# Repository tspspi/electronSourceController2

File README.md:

# Electron gun power supply and monitoring controller

_Note_: This project is designed for a particular experiment so it will not
be much of use for anyone who's not working on exactly that experiment.

This is firmware for a simple electron gun controller that is controlling

* Up to four FUG HCP 14-6500 high voltage power supplies (acceleration
  voltage, Wehnelt cylinder, focus voltage and a single deflection voltage
  power supply)
* The voltage and current measured by FUG HCP 14-6500 can also be used for
  general monitoring and beam loss measurement

## External communication ports

* UART0 provides main communication interface (and is also used by avrdude
  during flashing - there is an Arduino bootloader flashed on the board so
  flash method ```ẁiring``` can be used via USB

* Other UARTs may be used for RS485 or other components later on

## Pin assignment

| Pin | Assignment                          | Mode                      | ATEMGA2560 Port / Pin |
| --- | ----------------------------------- | ------------------------- | --------------------- |
| 22  | PSU1: Output enable                 | Digital out (optocoupled) | PA0                   |
| 23  | PSU1: Polarity set                  | Digital out (optocoupled) | PA1                   |
| 24  | PSU1: Current control mode          | Digital in                | PA2                   |
| 25  | PSU1: Voltage control mode          | Digital in                | PA3                   |
| 42  | PSU1: Voltage set                   | Analog out                | PL7                   |
| 43  | PSU1: Current limit set             | Analog out                | PL6                   |
| A0  | PSU1: Voltage sense                 | Analog in                 | PF0                   |
| A1  | PSU1: Current sense                 | Analog in                 | PF1                   |
| 26  | PSU2: Output enable                 | Digital out (optocoupled) | PA4                   |
| 27  | PSU2: Polarity set                  | Digital out (optocoupled) | PA5                   |
| 28  | PSU2: Current control mode          | Digital in                | PA6                   |
| 29  | PSU2: Voltage control mode          | Digital in                | PA7                   |
| 44  | PSU2: Voltage set                   | Analog out                | PL5                   |
| 45  | PSU2: Current limit set             | Analog out                | PL4                   |
| A2  | PSU2: Voltage sense                 | Analog in                 | PF2                   |
| A3  | PSU2: Current sense                 | Analog in                 | PF3                   |
| 30  | PSU3: Output enable                 | Digital out (optocoupled) | PC7                   |
| 31  | PSU3: Polarity set                  | Digital out (optocoupled) | PC6                   |
| 32  | PSU3: Current control mode          | Digital in                | PC5                   |
| 33  | PSU3: Voltage control mode          | Digital in                | PC4                   |
| 46  | PSU3: Voltage set                   | Analog out                | PL3                   |
| 47  | PSU3: Current limit set             | Analog out                | PL2                   |
| A4  | PSU3: Voltage sense                 | Analog in                 | PF4                   |
| A5  | PSU3: Current sense                 | Analog in                 | PF5                   |
| 34  | PSU4: Output enable                 | Digital out (optocoupled) | PC3                   |
| 35  | PSU4: Polarity set                  | Digital out (optocoupled) | PC2                   |
| 36  | PSU4: Current control mode          | Digital in                | PC1                   |
| 37  | PSU4: Voltage control mode          | Digital in                | PC0                   |
| 48  | PSU4: Voltage set                   | Analog out                | PL1                   |
| 49  | PSU4: Current limit set             | Analog out                | PL0                   |
| A6  | PSU4: Voltage sense                 | Analog in                 | PF6                   |
| A7  | PSU4: Current sense                 | Analog in                 | PF7                   |
| 38  | Filament power supply (230V side)   | Digital out               | PD7                   |
| A8  | Current sensor for filament         | Analog in                 | PK0                   |
| 50  | AD7705 MISO                         | Digital in                | PB3                   |
| 51  | AD7705 MOSI                         | Digital out               | PB2                   |
| 52  | AD7705 SCK                          | Digital out               | PB1                   |
| 53  | AD7705 CS                           | Digital out               | PB0                   |
|PWM10| AD7705 Reset                        | Digital out               | PB4                   |
|PWM11| AD7705 data ready                   | Digital in                | PB5                   |

## Protocol

In contrast to other implementations this board supports an ASCII based
communication protocol. For synchronization all messages start with a
fixed synchronization pattern consisting of three dollar signs. Each command
is terminated via a CR LF or only LF (CR is simply ignored by the serial
parser). Numbers are transmitted as ASCII decimal numbers.

| Command                                 | Sequence               | Response                                                                                                                     | Status                           |
| --------------------------------------- | ---------------------- | ---------------------------------------------------------------------------------------------------------------------------- | -------------------------------- |
| ID                                      | $$$ID<LF>              | Sends a simple ID response that identifies the firmware (ex. ```$$$electronctrl_20210707_001<LF>```)                         | working, tested                  |
| Filament on                             | $$$FILON<LF>           | Switches filament power supply on                                                                                            | working, tested                  |
| Filament off                            | $$$FILOFF<LF>          | Switches filament power supply off                                                                                           | working, tested                  |
| Estimate beam current                   | $$$BEAMA<LF>           | Calculates estimated beam current in 1/10 of microamperes                                                                    |                                  |
| Beam on                                 | $$$BEAMON<LF>          | Switches beam high voltage on (slowly, performing insulation test)                                                           | working, tested                  |
| Beam HV off                             | $$$BEAMHVOFF<LF>       | Switches beam high voltage off                                                                                               | working, tested                  |
| Get PSU current                         | $$$PSUGETA[n]<LF>      | Gets current for power supply 1,2,3,4                                                                                        | working, tested                  |
| Get PSU voltage                         | $$$PSUGETV[n]<LF>      | Gets voltage for power supply 1,2,3,4                                                                                        | working, tested                  |
| Get PSU modes                           | $$$PSUMODE<LF>         | Gets the mode for each PSU as a sequence of 4 ASCII chars (A or V for current or voltage controled mode, - for disabled)     | working, tested                  |
| Set PSU current limit                   | $$$PSUSETA[n][mmm]<LF> | Sets the power supply current limit for one of the 4 PSUs. The limit is supplied in 1/10 of an microampere                   | working, tested                  |
| Set PSU target voltage                  | $$$PSUSETV[n][mmm]<LF> | Sets the power supply voltage for one of the 4 PSUs. The voltage is set in V                                                 | working, tested                  |
| Set PSU polarity                        | $$$PSUPOL[n][p/n]<LF>  | Sets the polarity to be positive or negative                                                                                 | working, tested                  |
| Set PSU output enable                   | $$$PSUON[n]<LF>        | Enabled the output of the given PSU                                                                                          | working, tested                  |
| Set PSU output disable                  | $$$PSUOFF[n]<LF>       | Disabled the output of the given PSU                                                                                         | working, tested                  |
| Disable all voltages (PSU and filament) | $$$OFF<LF>             | Disabled all voltages including the filament supply                                                                          | working, tested                  |
| Get filament voltage                    | $$$FILV<LF>            | Measures filament voltage (if supported)                                                                                     |                                  |
| Get filament current                    | $$$FILA<LF>            | Measures filament current (if supported)                                                                                     |                                  |
| Set filament current                    | $$$SETFILA[n]<LF>      | Sets filament current via current controller board                                                                           |                                  |
| Perform HV insulation test              | $$$INSUL<LF>           | Performs insulation test. Reports voltages while testing.                                                                    | working, tested                  |
| Perform cathode bakeout                 | $$$FILBAKE<LF>         | Performs a baking sequence on filament to remove any residue of trapped gas on the surface                                   |                                  |
| Perform software reset                  | $$$RESET<LF>           | Performs a software reset on the control system (reinitializes everything, no power cycle)                                   |                                  |

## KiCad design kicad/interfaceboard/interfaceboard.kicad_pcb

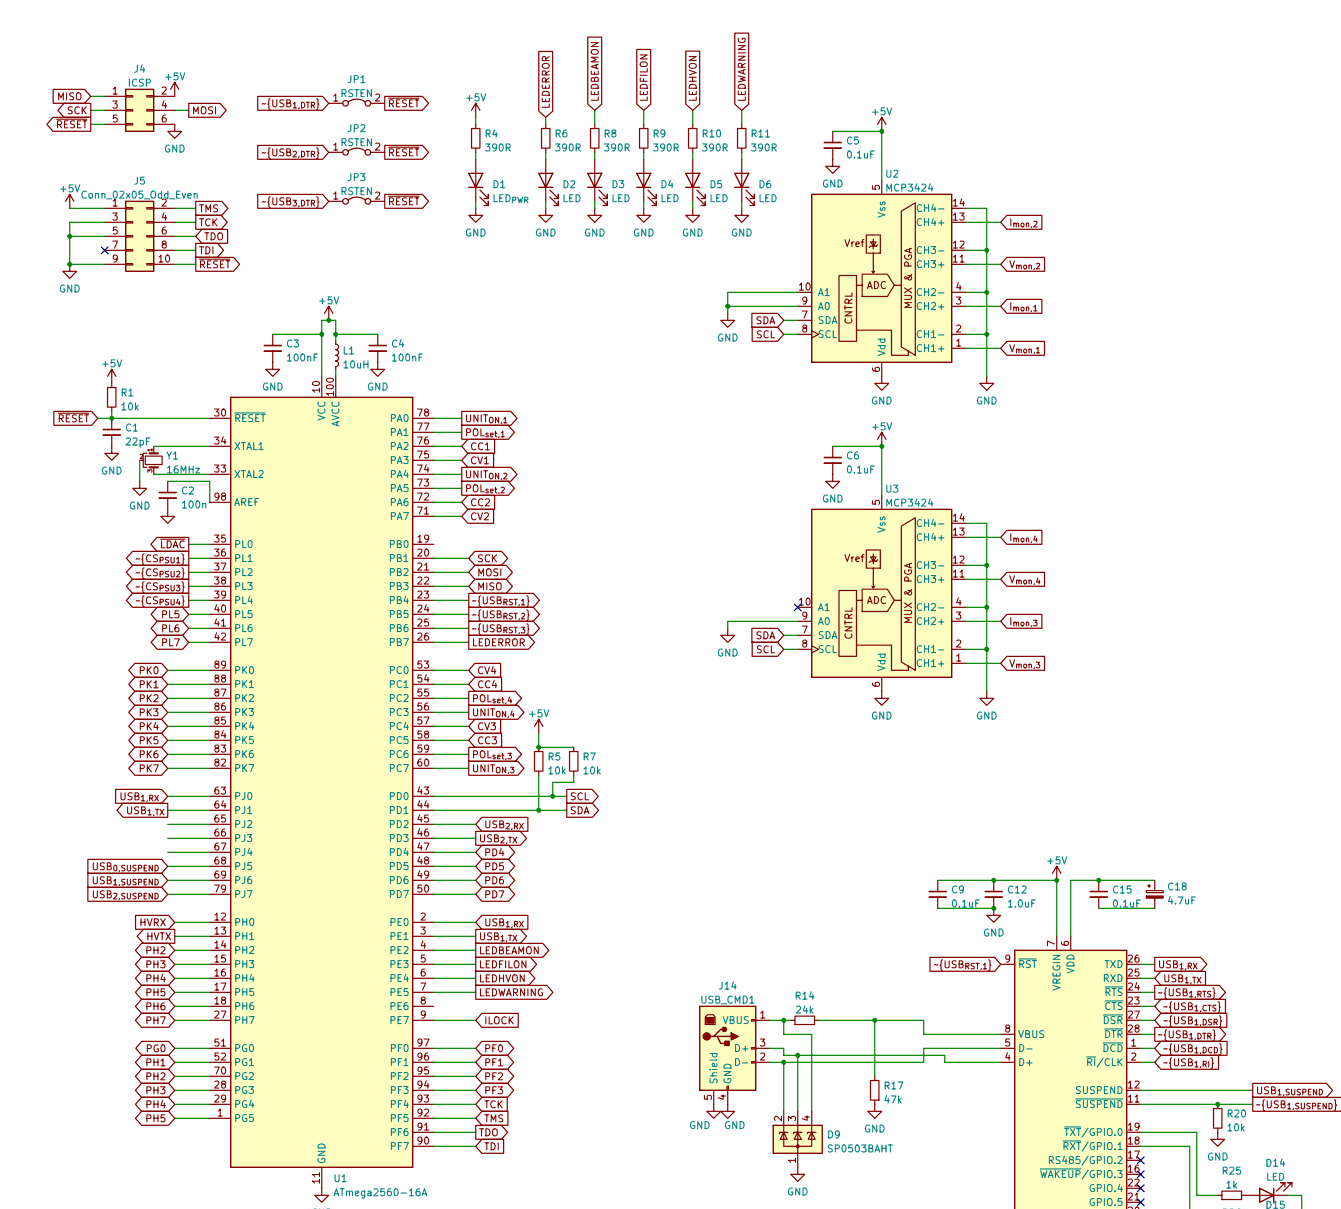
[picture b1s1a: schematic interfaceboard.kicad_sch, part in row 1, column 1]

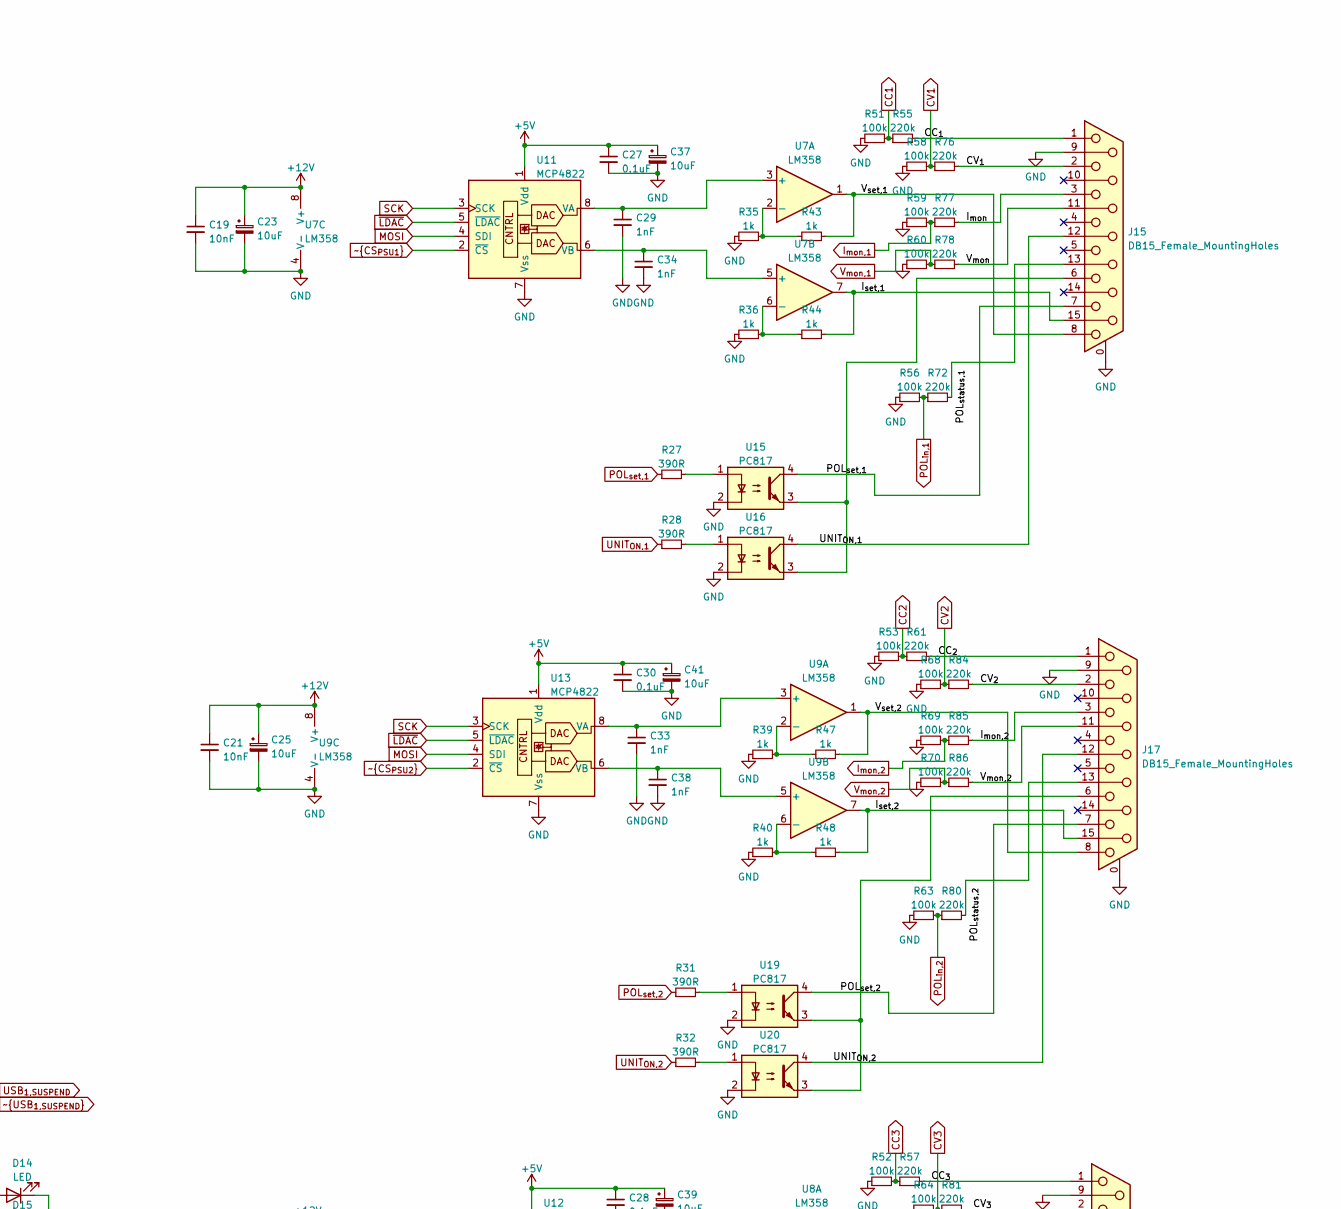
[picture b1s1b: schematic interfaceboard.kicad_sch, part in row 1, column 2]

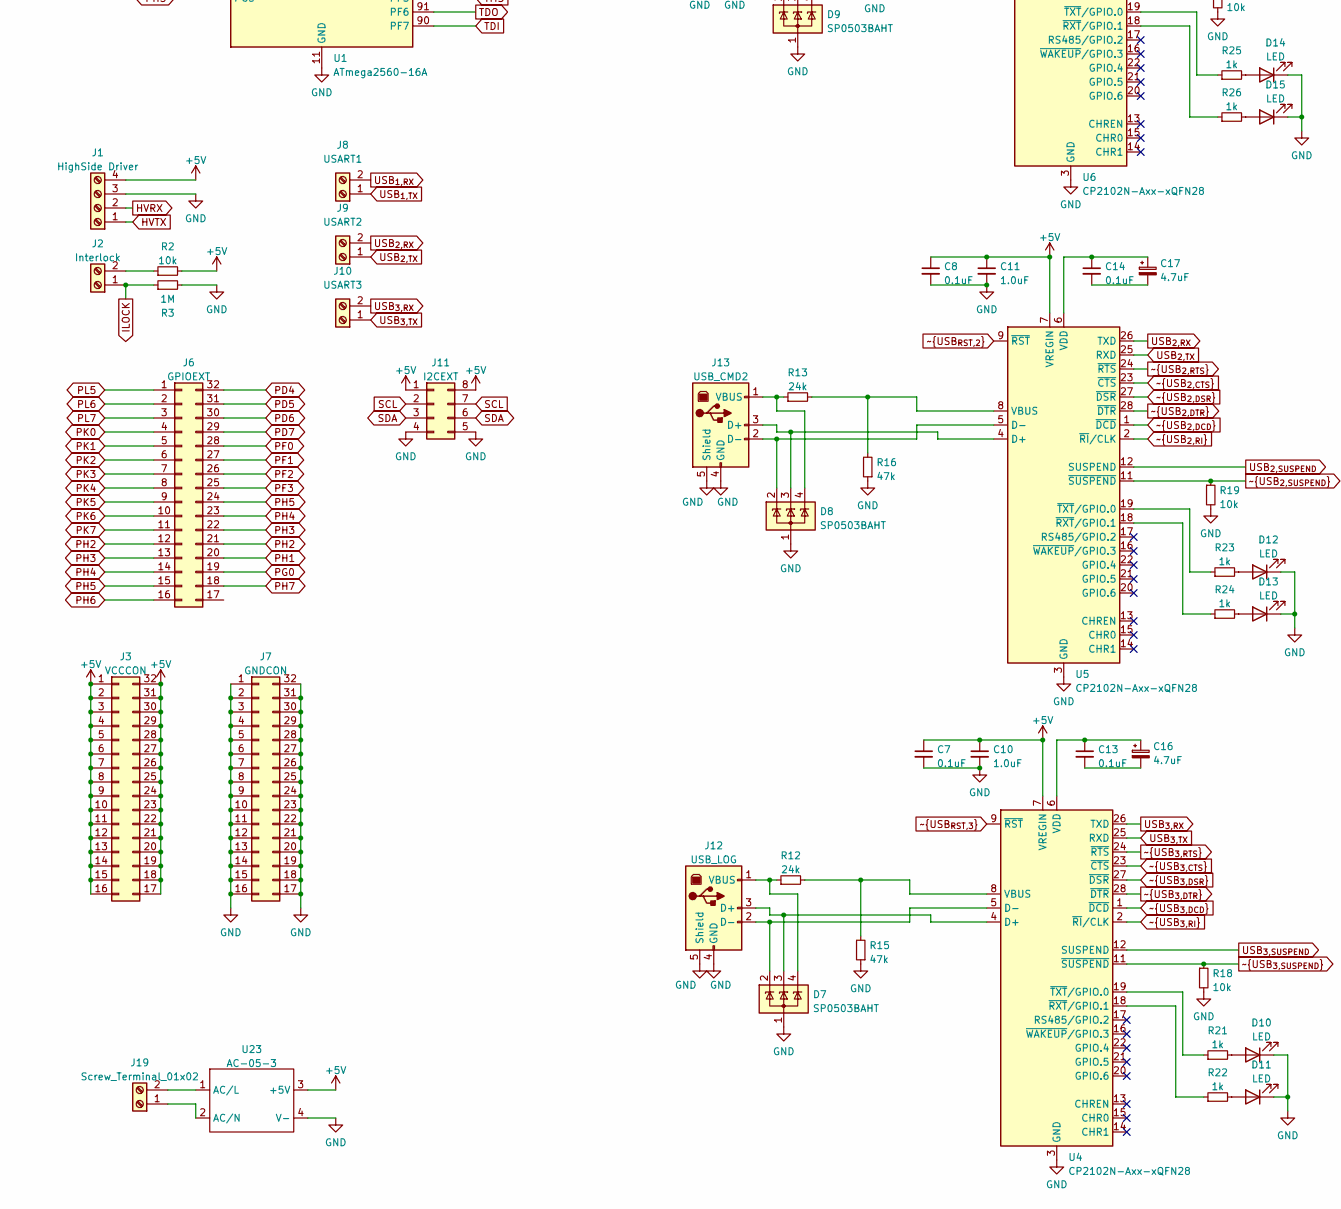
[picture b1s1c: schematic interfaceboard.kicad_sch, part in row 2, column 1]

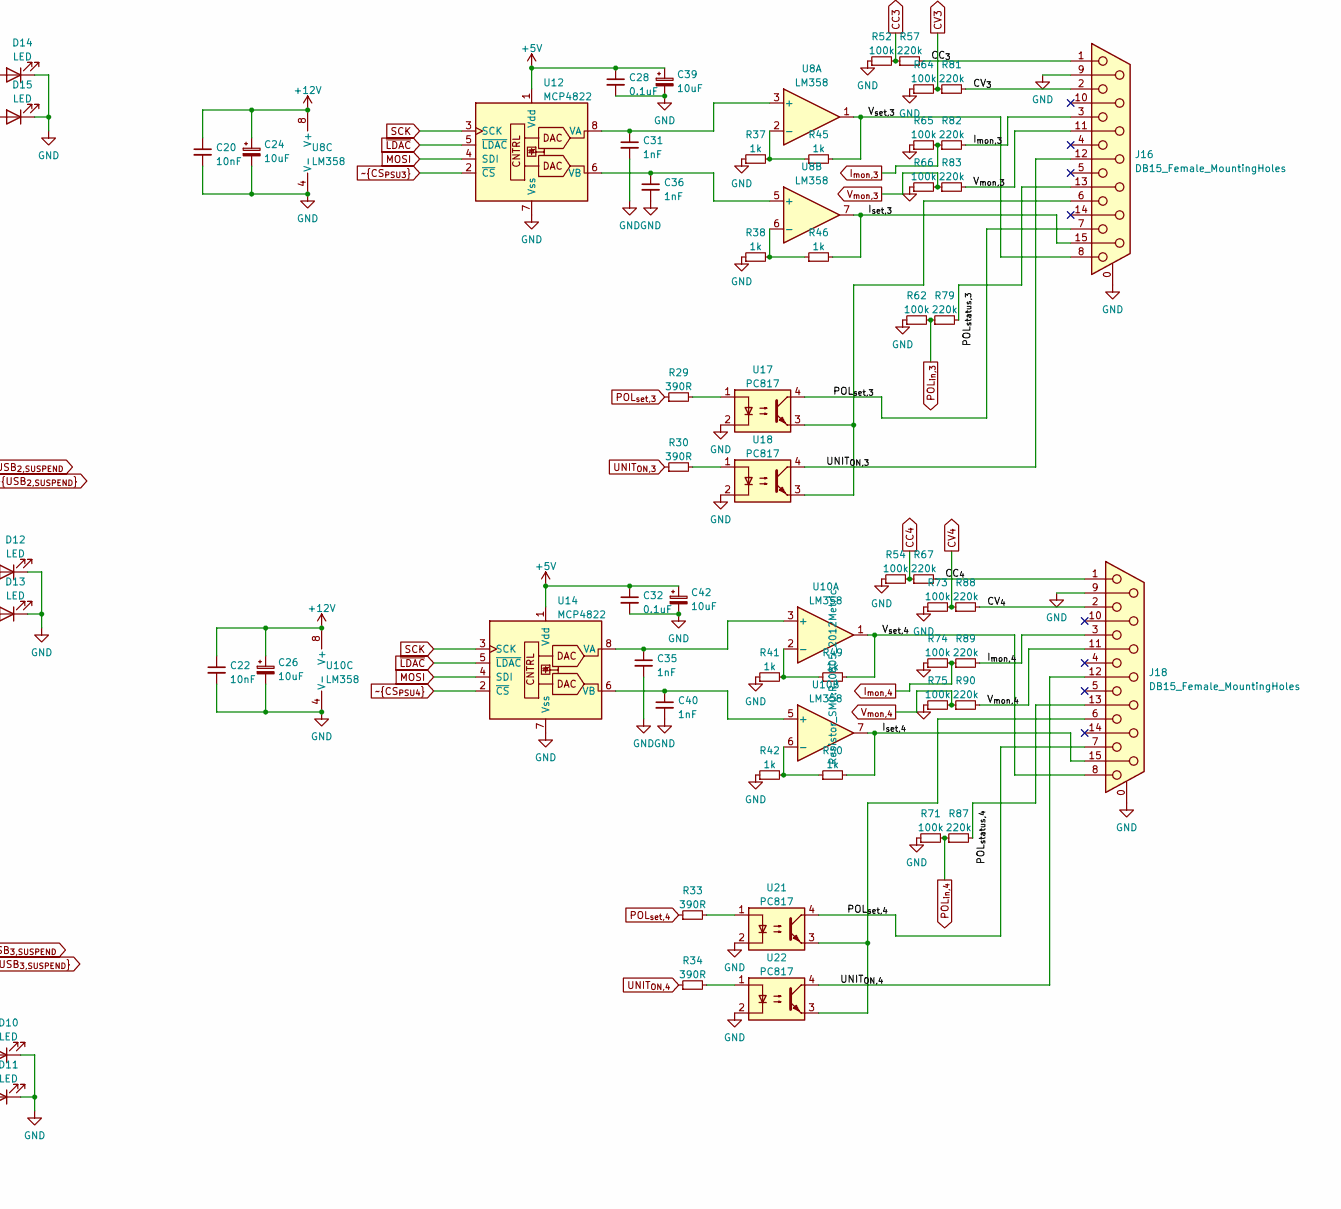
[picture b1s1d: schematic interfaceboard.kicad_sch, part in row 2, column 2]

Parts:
C1: 22pF; C_0805_2012Metric
C2: 100n; C_0805_2012Metric
C3, C4: 100nF; C_0805_2012Metric
C5, C6, C7, C8, C9, C13, C14, C15, C27, C28, C30, C32: 0.1uF; C_0805_2012Metric
C10, C11, C12: 1.0uF; C_0805_2012Metric
C16, C17, C18: 4.7uF; C_0805_2012Metric
C19, C20, C21, C22: 10nF; C_0805_2012Metric
C23, C24, C25, C26, C37, C39, C41, C42: 10uF; C_0805_2012Metric
C29, C31, C33, C34, C35, C36, C38, C40: 1nF; C_0805_2012Metric
D1: LED_{PWR}; LED_D3.0mm
D2, D3, D4, D5, D6, D10, D11, D12, D13, D14, D15: LED; LED_D3.0mm
D7, D8, D9: SP0503BAHT; SOT-143
J1: HighSide Driver; PinHeader_1x04_P2.54mm_Vertical
J2: Interlock; PinHeader_1x02_P2.54mm_Vertical
J3: VCCCON; PinHeader_2x16_P2.54mm_Vertical
J4: ICSP; PinSocket_2x03_P2.54mm_Vertical
J5: Conn_02x05_Odd_Even; PinSocket_2x05_P2.54mm_Vertical
J6: GPIOEXT; PinHeader_2x16_P2.54mm_Vertical
J7: GNDCON; PinHeader_2x16_P2.54mm_Vertical
J8: USART1; PinHeader_1x02_P2.54mm_Vertical
J9: USART2; PinHeader_1x02_P2.54mm_Vertical
J10: USART3; PinHeader_1x02_P2.54mm_Vertical
J11: I2CEXT; PinHeader_2x04_P2.54mm_Vertical
J12: USB_LOG; USB_B_Lumberg_2411_02_Horizontal; FarnellNo 3490505 (2401 06)
J13: USB_CMD2; USB_B_Lumberg_2411_02_Horizontal
J14: USB_CMD1; USB_B_Lumberg_2411_02_Horizontal
J15: DB15_Female_MountingHoles; DSUB-15_Female_Horizontal_P2.77x2.84mm_EdgePinOffset9.90mm_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; FarnellNo 3817870
J16, J17, J18: DB15_Female_MountingHoles; DSUB-15_Female_Horizontal_P2.77x2.84mm_EdgePinOffset9.90mm_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
J19: Screw_Terminal_01x02; PinHeader_1x02_P2.54mm_Vertical
JP1, JP2, JP3: RSTEN; PinSocket_1x02_P2.54mm_Vertical
L1: 10uH; L_1206_3216Metric
R1, R2, R5, R7, R18, R19, R20: 10k; R_0805_2012Metric
R3: 1M; R_0805_2012Metric
R4, R6, R8, R9, R10, R11, R27, R28, R29, R30, R31, R32, R33, R34: 390R; R_0805_2012Metric
R12, R13, R14: 24k; R_0805_2012Metric
R15, R16, R17: 47k; R_0805_2012Metric
R21, R22, R23, R24, R25, R26, R35, R36, R37, R38, R39, R40, R41, R42, R43, R44, R45, R46, R47, R48, R49, R50: 1k; R_0805_2012Metric
R51, R52, R53, R54, R56, R58, R59, R60, R62, R63, R64, R65, R66, R68, R69, R70, R71, R73, R74, R75: 100k; R_0805_2012Metric
R55, R57, R61, R67, R72, R76, R77, R78, R79, R80, R81, R82, R83, R84, R85, R86, R87, R88, R89, R90: 220k; R_0805_2012Metric
U1: ATmega2560-16A; TQFP-100_14x14mm_P0.5mm
U2, U3: MCP3424; SOIC-14_3.9x8.7mm_P1.27mm
U4, U5, U6: CP2102N-Axx-xQFN28; QFN-28-1EP_5x5mm_P0.5mm_EP3.35x3.35mm
U7, U8, U9, U10: LM358; DIP-8_W7.62mm
U11, U12, U13, U14: MCP4822; DIP-8_W7.62mm
U15, U16, U17, U18, U19, U20, U21, U22: PC817; DIP-4_W7.62mm
U23: AC-05-3
Y1: 16MHz; PinSocket_1x03_P2.54mm_Vertical

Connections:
+5V: C3.1, C4.1, C5.1, C6.1, C7.1, C8.1, C9.1, C10.1, C11.1, C12.1, C27.1, C28.1, C30.1, C32.1, C37.1, C39.1, C41.1, C42.1, J1.4, J3.1, J3.2, J3.3, J3.4, J3.5, J3.6, J3.7, J3.8, J3.9, J3.10, J3.11, J3.12, J3.13, J3.14, J3.15, J3.16, J3.17, J3.18, J3.19, J3.20, J3.21, J3.22, J3.23, J3.24, J3.25, J3.26, J3.27, J3.28, J3.29, J3.30, J3.31, J3.32, J4.2, J5.1, J11.1, J11.8, L1.1, R1.1, R2.2, R4.1, R5.1, R7.1, U1.10 (VCC), U1.31 (VCC), U1.61 (VCC), U1.80 (VCC), U2.5 (Vss), U3.5 (Vss), U4.7 (VREGIN), U5.7 (VREGIN), U6.7 (VREGIN), U11.1 (Vdd), U12.1 (Vdd), U13.1 (Vdd), U14.1 (Vdd), U23.3 (+5V)
+12V: C19.1, C20.1, C21.1, C22.1, C23.1, C24.1, C25.1, C26.1, U7.8 (V+), U8.8 (V+), U9.8 (V+), U10.8 (V+)
/CC_{1}: J15.1, R55.2
/CC_{2}: J17.1, R61.2
/CC_{3}: J16.1, R57.2
/CC_{4}: J18.1, R67.2
/CV_{1}: J15.2, R76.2
/CV_{2}: J17.2, R84.2
/CV_{3}: J16.2, R81.2
/CV_{4}: J18.2, R88.2
/I_{mon}: J15.3, R77.2
/I_{set,1}: J15.15, R44.2, U7.7
/I_{set,2}: J17.15, R48.2, U9.7
/I_{set,3}: J16.15, R46.2, U8.7
/I_{set,4}: J18.15, R50.2, U10.7
/V_{mon}: J15.11 (P111), R78.2
/V_{set,1}: J15.8, R43.2, U7.1
/V_{set,2}: J17.8, R47.2, U9.1
/V_{set,3}: J16.8, R45.2, U8.1
/V_{set,4}: J18.8, R49.2, U10.1
CC1: R51.2, R55.1, U1.76 (PA2)
CC2: R53.2, R61.1, U1.72 (PA6)
CC3: R52.2, R57.1, U1.58 (PC5)
CC4: R54.2, R67.1, U1.54 (PC1)
CV1: R58.2, R76.1, U1.75 (PA3)
CV2: R68.2, R84.1, U1.71 (PA7)
CV3: R64.2, R81.1, U1.57 (PC4)
CV4: R73.2, R88.1, U1.53 (PC0)
GND: C1.2, C2.2, C3.2, C4.2, C5.2, C6.2, C7.2, C8.2, C9.2, C10.2, C11.2, C12.2, C19.2, C20.2, C21.2, C22.2, C23.2, C24.2, C25.2, C26.2, C27.2, C28.2, C29.2, C30.2, C31.2, C32.2, C33.2, C34.2, C35.2, C36.2, C37.2, C38.2, C39.2, C40.2, C41.2, C42.2, D1.1 (K), D2.1 (K), D3.1 (K), D4.1 (K), D5.1 (K), D6.1 (K), D7.1 (A), D8.1 (A), D9.1 (A), D10.1 (K), D11.1 (K), D12.1 (K), D13.1 (K), D14.1 (K), D15.1 (K), J1.3, J4.6, J5.3, J5.5, J5.9, J7.1, J7.2, J7.3, J7.4, J7.5, J7.6, J7.7, J7.8, J7.9, J7.10, J7.11, J7.12, J7.13, J7.14, J7.15, J7.16, J7.17, J7.18, J7.19, J7.20, J7.21, J7.22, J7.23, J7.24, J7.25, J7.26, J7.27, J7.28, J7.29, J7.30, J7.31, J7.32, J11.4, J11.5, J12.4 (GND), J12.5 (Shield), J13.4 (GND), J13.5 (Shield), J14.4 (GND), J14.5 (Shield), J15.0 (PAD), J15.9, J16.0 (PAD), J16.9, J17.0 (PAD), J17.9, J18.0 (PAD), J18.9, R3.2, R15.1, R16.1, R17.1, R18.2, R19.2, R20.2, R35.1, R36.1, R37.1, R38.1, R39.1, R40.1, R41.1, R42.1, R51.1, R52.1, R53.1, R54.1, R56.1, R58.1, R59.1, R60.1, R62.1, R63.1, R64.1, R65.1, R66.1, R68.1, R69.1, R70.1, R71.1, R73.1, R74.1, R75.1, U1.11 (GND), U1.32 (GND), U1.62 (GND), U1.81 (GND), U1.99 (GND), U2.2 (CH1-), U2.4 (CH2-), U2.6 (Vdd), U2.9 (A0), U2.10 (A1), U2.12 (CH3-), U2.14 (CH4-), U3.2 (CH1-), U3.4 (CH2-), U3.6 (Vdd), U3.9 (A0), U3.12 (CH3-), U3.14 (CH4-), U4.3 (GND), U4.29 (GND), U5.3 (GND), U5.29 (GND), U6.3 (GND), U6.29 (GND), U7.4 (V-), U8.4 (V-), U9.4 (V-), U10.4 (V-), U11.7 (Vss), U12.7 (Vss), U13.7 (Vss), U14.7 (Vss), U15.2, U16.2, U17.2, U18.2, U19.2, U20.2, U21.2, U22.2, U23.4 (V-), Y1.2
HVRX: J1.2, U1.12 (PH0)
HVTX: J1.1, U1.13 (PH1)
ILOCK: J2.1, R3.1, U1.9 (PE7)
I_{mon,1}: R59.2, R77.1, U2.3 (CH2+)
I_{mon,2}: J17.3, R69.2, R85.1, R85.2, U2.13 (CH4+)
I_{mon,3}: J16.3, R65.2, R82.1, R82.2, U3.3 (CH2+)
I_{mon,4}: J18.3, R74.2, R89.1, R89.2, U3.13 (CH4+)
LEDBEAMON: R8.1, U1.4 (PE2)
LEDERROR: R6.1, U1.26 (PB7)
LEDFILON: R9.1, U1.5 (PE3)
LEDHVON: R10.1, U1.6 (PE4)
LEDWARNING: R11.1, U1.7 (PE5)
MISO: J4.1, U1.22 (PB3)
MOSI: J4.4, U1.21 (PB2), U11.4 (SDI), U12.4 (SDI), U13.4 (SDI), U14.4 (SDI)
unnamed: C2.1, U1.98 (AREF)
unnamed: C13.1, C16.1, U4.6 (VDD)
unnamed: C13.2, C16.2
unnamed: C14.1, C17.1, U5.6 (VDD)
unnamed: C14.2, C17.2
unnamed: C15.1, C18.1, U6.6 (VDD)
unnamed: C15.2, C18.2
unnamed: C29.1, U7.3 (+), U11.8 (VA)
unnamed: C31.1, U8.3 (+), U12.8 (VA)
unnamed: C33.1, U9.3 (+), U13.8 (VA)
unnamed: C34.1, U7.5 (+), U11.6 (VB)
unnamed: C35.1, U10.3 (+), U14.8 (VA)
unnamed: C36.1, U8.5 (+), U12.6 (VB)
unnamed: C38.1, U9.5 (+), U13.6 (VB)
unnamed: C40.1, U10.5 (+), U14.6 (VB)
unnamed: D1.2 (A), R4.2
unnamed: D2.2 (A), R6.2
unnamed: D3.2 (A), R8.2
unnamed: D4.2 (A), R9.2
unnamed: D5.2 (A), R10.2
unnamed: D6.2 (A), R11.2
unnamed: D7.2 (K), J12.2 (D-), U4.5 (D-)
unnamed: D7.3 (K), J12.3 (D+), U4.4 (D+)
unnamed: D7.4 (K), J12.1 (VBUS), R12.1
unnamed: D8.2 (K), J13.2 (D-), U5.5 (D-)
unnamed: D8.3 (K), J13.3 (D+), U5.4 (D+)
unnamed: D8.4 (K), J13.1 (VBUS), R13.1
unnamed: D9.2 (K), J14.2 (D-), U6.5 (D-)
unnamed: D9.3 (K), J14.3 (D+), U6.4 (D+)
unnamed: D9.4 (K), J14.1 (VBUS), R14.1
unnamed: D10.2 (A), R21.2
unnamed: D11.2 (A), R22.2
unnamed: D12.2 (A), R23.2
unnamed: D13.2 (A), R24.2
unnamed: D14.2 (A), R25.2
unnamed: D15.2 (A), R26.2
unnamed: J2.2, R2.1
unnamed: J15.6, U15.3, U16.3
unnamed: J15.13, R72.2
unnamed: J16.6, U17.3, U18.3
unnamed: J16.13, R79.2
unnamed: J17.6, U19.3, U20.3
unnamed: J17.13, R80.2
unnamed: J18.6, U21.3, U22.3
unnamed: J18.13, R87.2
unnamed: J19.1, U23.2 (AC/N)
unnamed: J19.2, U23.1 (AC/L)
unnamed: L1.2, U1.100 (AVCC)
unnamed: R12.2, R15.2, U4.8 (VBUS)
unnamed: R13.2, R16.2, U5.8 (VBUS)
unnamed: R14.2, R17.2, U6.8 (VBUS)
unnamed: R21.1, U4.19 (~TXT/GPIO.0)
unnamed: R22.1, U4.18 (~RXT/GPIO.1)
unnamed: R23.1, U5.19 (~TXT/GPIO.0)
unnamed: R24.1, U5.18 (~RXT/GPIO.1)
unnamed: R25.1, U6.19 (~TXT/GPIO.0)
unnamed: R26.1, U6.18 (~RXT/GPIO.1)
unnamed: R27.2, U15.1
unnamed: R28.2, U16.1
unnamed: R29.2, U17.1
unnamed: R30.2, U18.1
unnamed: R31.2, U19.1
unnamed: R32.2, U20.1
unnamed: R33.2, U21.1
unnamed: R34.2, U22.1
unnamed: R35.2, R43.1, U7.2 (-)
unnamed: R36.2, R44.1, U7.6 (-)
unnamed: R37.2, R45.1, U8.2 (-)
unnamed: R38.2, R46.1, U8.6 (-)
unnamed: R39.2, R47.1, U9.2 (-)
unnamed: R40.2, R48.1, U9.6 (-)
unnamed: R41.2, R49.1, U10.2 (-)
unnamed: R42.2, R50.1, U10.6 (-)
unnamed: U1.33 (XTAL2), Y1.3
unnamed: U1.34 (XTAL1), Y1.1
PD4: J6.32, U1.47 (PD4)
PD5: J6.31, U1.48 (PD5)
PD6: J6.30, U1.49 (PD6)
PD7: J6.29, U1.50 (PD7)
PF0: J6.28, U1.97 (PF0)
PF1: J6.27, U1.96 (PF1)
PF2: J6.26, U1.95 (PF2)
PF3: J6.25, U1.94 (PF3)
PG0: J6.19, U1.51 (PG0)
PH1: J6.20, U1.52 (PG1)
PH2: J6.12, J6.21, U1.14 (PH2), U1.70 (PG2)
PH3: J6.13, J6.22, U1.15 (PH3), U1.28 (PG3)
PH4: J6.14, J6.23, U1.16 (PH4), U1.29 (PG4)
PH5: J6.15, J6.24, U1.1 (PG5), U1.17 (PH5)
PH6: J6.16, U1.18 (PH6)
PH7: J6.18, U1.27 (PH7)
PK0: J6.4, U1.89 (PK0)
PK1: J6.5, U1.88 (PK1)
PK2: J6.6, U1.87 (PK2)
PK3: J6.7, U1.86 (PK3)
PK4: J6.8, U1.85 (PK4)
PK5: J6.9, U1.84 (PK5)
PK6: J6.10, U1.83 (PK6)
PK7: J6.11, U1.82 (PK7)
PL5: J6.1, U1.40 (PL5)
PL6: J6.2, U1.41 (PL6)
PL7: J6.3, U1.42 (PL7)
POL_{in,1}: R56.2, R72.1
POL_{in,2}: R63.2, R80.1
POL_{in,3}: R62.2, R79.1
POL_{in,4}: R71.2, R87.1
POL_{set,1}: J15.7, R27.1, U1.77 (PA1), U15.4
POL_{set,2}: J17.7, R31.1, U1.73 (PA5), U19.4
POL_{set,3}: J16.7, R29.1, U1.59 (PC6), U17.4
POL_{set,4}: J18.7, R33.1, U1.55 (PC2), U21.4
SCK: J4.3, U1.20 (PB1), U11.3 (SCK), U12.3 (SCK), U13.3 (SCK), U14.3 (SCK)
SCL: J11.2, J11.7, R7.2, U1.43 (PD0), U2.8 (SCL), U3.8 (SCL)
SDA: J11.3, J11.6, R5.2, U1.44 (PD1), U2.7 (SDA), U3.7 (SDA)
TCK: J5.4, U1.93 (PF4)
TDI: J5.8, U1.90 (PF7)
TDO: J5.6, U1.91 (PF6)
TMS: J5.2, U1.92 (PF5)
UNIT_{ON,1}: J15.12, R28.1, U1.78 (PA0), U16.4
UNIT_{ON,2}: J17.12, R32.1, U1.74 (PA4), U20.4
UNIT_{ON,3}: J16.12, R30.1, U1.60 (PC7), U18.4
UNIT_{ON,4}: J18.12, R34.1, U1.56 (PC3), U22.4
USB_{0,SUSPEND}: U1.68 (PJ5)
USB_{1,RX}: J8.2, U1.2 (PE0), U1.63 (PJ0), U6.26 (TXD)
USB_{1,SUSPEND}: U1.69 (PJ6), U6.12 (SUSPEND)
USB_{1,TX}: J8.1, U1.3 (PE1), U1.64 (PJ1), U6.25 (RXD)
USB_{2,RX}: J9.2, U1.45 (PD2), U5.26 (TXD)
USB_{2,SUSPEND}: U1.79 (PJ7), U5.12 (SUSPEND)
USB_{2,TX}: J9.1, U1.46 (PD3), U5.25 (RXD)
USB_{3,RX}: J10.2, U4.26 (TXD)
USB_{3,SUSPEND}: U4.12 (SUSPEND)
USB_{3,TX}: J10.1, U4.25 (RXD)
V_{mon,1}: R60.2, R78.1, U2.1 (CH1+)
V_{mon,2}: J17.11 (P111), R70.2, R86.1, R86.2, U2.11 (CH3+)
V_{mon,3}: J16.11 (P111), R66.2, R83.1, R83.2, U3.1 (CH1+)
V_{mon,4}: J18.11 (P111), R75.2, R90.1, R90.2, U3.11 (CH3+)
~CS_{PSU1}: U1.36 (PL1), U11.2 (~CS)
~CS_{PSU2}: U1.37 (PL2), U13.2 (~CS)
~CS_{PSU3}: U1.38 (PL3), U12.2 (~CS)
~CS_{PSU4}: U1.39 (PL4), U14.2 (~CS)
~LDAC: U1.35 (PL0), U11.5 (~LDAC), U12.5 (~LDAC), U13.5 (~LDAC), U14.5 (~LDAC)
~RESET: C1.1, J4.5, J5.10, JP1.2 (B), JP2.2 (B), JP3.2 (B), R1.2, U1.30 (~RESET)
~USB_{1,CTS}: U6.23 (~CTS)
~USB_{1,DCD}: U6.1 (~DCD)
~USB_{1,DSR}: U6.27 (~DSR)
~USB_{1,DTR}: JP1.1 (A), U6.28 (~DTR)
~USB_{1,RI}: U6.2 (~RI/CLK)
~USB_{1,RTS}: U6.24 (~RTS)
~USB_{1,SUSPEND}: R20.1, U6.11 (~SUSPEND)
~USB_{2,CTS}: U5.23 (~CTS)
~USB_{2,DCD}: U5.1 (~DCD)
~USB_{2,DSR}: U5.27 (~DSR)
~USB_{2,DTR}: JP2.1 (A), U5.28 (~DTR)
~USB_{2,RI}: U5.2 (~RI/CLK)
~USB_{2,RTS}: U5.24 (~RTS)
~USB_{2,SUSPEND}: R19.1, U5.11 (~SUSPEND)
~USB_{3,CTS}: U4.23 (~CTS)
~USB_{3,DCD}: U4.1 (~DCD)
~USB_{3,DSR}: U4.27 (~DSR)
~USB_{3,DTR}: JP3.1 (A), U4.28 (~DTR)
~USB_{3,RI}: U4.2 (~RI/CLK)
~USB_{3,RTS}: U4.24 (~RTS)
~USB_{3,SUSPEND}: R18.1, U4.11 (~SUSPEND)
~USB_{RST,1}: U1.23 (PB4), U6.9 (~RST)
~USB_{RST,2}: U1.24 (PB5), U5.9 (~RST)
~USB_{RST,3}: U1.25 (PB6), U4.9 (~RST)

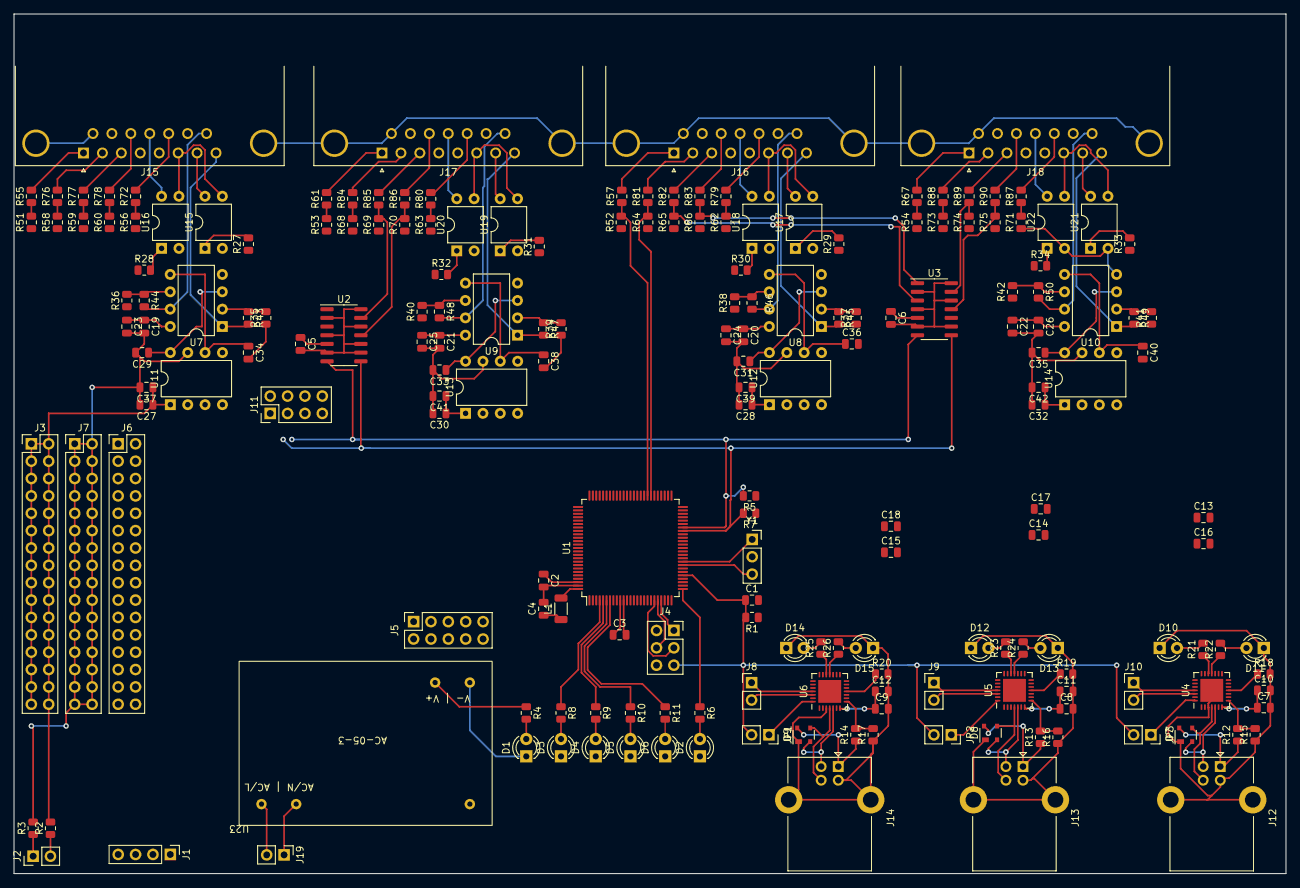
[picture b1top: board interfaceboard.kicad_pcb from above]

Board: 2 copper layers, 186.1 x 125.7 mm, 194 parts (0 on the bottom side), 191 nets.

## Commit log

2021-07-07 Added temporary directory
2021-07-07 Template for host controller software
2021-07-07 Added missing gitignore
2021-07-07 Fixed message decoding
2021-07-07 Updated gitignore
2021-07-07 Building static library for controller, separated from CLI
2021-07-07 Implemented simple ID command, simply dumping serial response currently
2021-07-07 Added pin assignment and ID command
2021-07-07 Added mapping to pin/port pairs
2021-07-07 Added list of commands
2021-07-07 Fixed table
2021-07-07 Added status column
2021-07-07 Added GPIO initialization
2021-07-08 Missing library dependency for the CLI utility
2021-07-08 Added termination / release function
2021-07-08 Removed NULL byte transmitted after current messages
2021-07-08 Ringbuffer for receiving of messages
2021-07-08 Fixed resynchronization (part 1)
2021-07-08 Longer delay after reset
2021-07-08 Fixed resynchronization
2021-07-08 Added ADC initialization
2021-07-09 Added external declaration for current ADC values
2021-07-09 Fixed ADC issues
2021-07-09 Removed unnecessary comment
2021-07-09 Increased startup delay
2021-07-09 Removed unnecessary CR
2021-07-09 Added serialization function for unsigned integers to ASCII decimal
2021-07-09 Added support for current and voltage measurement (raw ADC counts)
2021-07-09 Removed unneccesary configuration external
2021-07-09 Implemented V and A conversion for HCP, fixed reply format
2021-07-09 HCP: Implemented query functions for current and voltage
2021-07-09 Updated voltage measurement calibration ...
2021-07-09 Added PSU module
2021-07-09 Adding ability to set PSU polarity on all 4 PSUs
2021-07-09 Implementes PSU ON and PSU OFF commands
2021-07-09 Implementes PSU polarity and enabled functions
2021-07-13 Added PWM routines to set voltage and current and provided coarse calibration
2021-07-13 Implemented set voltage and set current
2021-07-13 Added note
2021-07-13 Minor fix
2021-07-13 Removed debug code
2021-07-13 Allowing upload of firmware image (ihex)
2021-07-13 Adding current version
2021-07-26 Changed BAUD from 115200 -> 19200; fixed minor bugs
2021-07-29 Modified output routines to perform only a single write on both PORTS
2021-07-29 Added support for filament PWM, fixed PWM frequencies
2021-07-29 Minor bugfixes
2021-07-29 Added support for 16 ADC channels
2021-08-16 New assignment for A8 for current measurement
2021-08-16 Moved to 16 channel ADC measurements, minor bugfix
2021-08-16 Added function to set PWM cycle count (for closed loop control)
2021-08-16 Bugfixes when using 16 ADC channels instead of 8
2021-08-16 Add support to read filament current in host CLI tool
2021-08-16 Added support for filament current sensor
2021-08-17 Implemented off, filament on and filament off commands
2021-08-17 Added host library support to send filament on/off and set filament current commands
2021-08-17 Off now also disabled filament current
2021-08-17 Fixed OFF - now also disables filament; updated README
2021-08-17 Implemented OFF in host library
2021-08-17 Implemented setting filament current (duty cycle, not mA currently)
2021-08-17 Implemented mode detection (off / voltage controlled / current limited) in serial handler
2021-08-17 Added support for PSU modes in host library
2021-08-17 Implemented insulation testing (and partially beam on) ramp
2021-08-17 Added host command to trigger insulation test
2021-08-17 Implemented BEAMHVOFF command
2021-08-17 Updated README to reflect BEAMHVOFF implementation
2021-08-17 Implemented beam on method
2021-08-17 Added beam on command
2021-08-17 Bumping version number
2021-08-17 Rebuilt binary
2021-08-18 Beam on now honors filament current setting, better reporting, ramp works, off disables PSUs
2021-08-18 Limit is now correct while we're loading PWM counts
2021-08-19 Moved current ramp in front of HV ramp to prevent cathode stripping
2021-08-20 Added usage and command line argument validation
2021-08-20 Added current measurement output to message
2021-08-20 Pushing current firmware revision
2021-08-20 Implemented basic CLI tool to run commands via serial interface
2021-09-07 Implemented status protocol for serial 2
2021-09-07 Added support for USART1 (same as USART0 but without resetting)
2021-09-08 Allocated pins for AD7705
2021-09-20 Fixed logging port implementation
2022-02-25 Adding first templates for library / UI
2022-03-02 Pythonification and synchronous methods (not restarting on error up until now)
2022-03-02 Missing files
2022-03-02 Adding missing setuptools section header
2022-03-02 Ignoring dist-files in source repo
2022-03-02 Ignoring egg-info
2022-03-02 README update to include a description of the content ...
2022-03-08 Faster ramp speed
2022-05-02 Bugfix: Introduce delay after initialization; bump version numer
2022-05-02 Missing package for sleep
2022-05-02 Commiting correct bugfix this time ...
2022-05-02 Added atexit routine to release serial port and shutdown thread
2022-05-04 Overcurrent detection only triggers if set voltage is not zero
2022-05-04 Calling off on atexit
2022-05-04 Added message on import
2022-05-04 Fixed typo in exception handling, adding delay for off
2022-05-04 Removed dead code
2022-05-04 Off also sets voltages to 0
2022-05-04 Speed up filament heating by 1/3
2022-05-04 Tuned warmup of filament
2022-05-05 Setting to zero now also affects first command channel
2022-05-05 Implementing reset command
2022-05-05 Reset to documentation
2022-05-05 Implemented jabber and soft reset functions
2022-06-22 Remove delay on connection (not necessary on secondary port)
2022-06-22 Bump version number
2022-06-22 Adding no-protection command to firmware
2022-06-22 Adding noprotection support to host library
2022-06-22 Adding support for noprotection in host cli
2022-06-27 Added new default value from quakesr
2022-07-20 Added quakEstimateBeamCurrent project specific beam current estimation
2022-07-20 Fixed invalid version string shown by eguncom.py
2022-07-20 Raising exception in beam current estimation method when not connected
2022-07-21 Fixed QUAK/ESR configuration VISA_ID_EBEAM
2022-07-21 New version
2022-07-22 Added delays
2022-07-26 Minor bug fix
2022-07-26 MQTT client side topic filter (sometimes used)
2022-07-26 Partial MQTT based client implementation
2022-07-26 Skeleton for MQTT based microservice interface
2022-09-20 Implemented retries on command timeouts
2022-09-20 Now Whenelt and Focus work again as expected as current sinks in the QUAK/ESR experiment
2022-09-20 Version 0.0.17
2022-09-20 Removed missing implementation for MQTT
2022-09-20 Remove lingering MQTT stuff
2022-09-20 Adding gitignore (ignoring frama-c output)
2022-09-20 Beginning basic ACSL annotation, removing dead code
2022-09-20 ACSL annotations
2022-09-20 Disable currently unused logging port
2022-09-21 Implemented synchronization by disabling interrupts in ringbuffer access routines, empty writes now write $'
2022-09-21 Bumping version including bugfixes, removing binary from source repo
2022-09-21 Adding binary again
2022-09-27 PHONY targets include flash and framac
2022-10-10 Decrease serial ringbuffer size from 1 KB -> 512 byte
2022-10-10 Bugfix: ringbuffer code would leave ISRs disabled
2022-10-10 Added current setting method for power supplies
2022-10-10 Version increase
2022-10-21 Update to use secondary current controller board instead of PWM via SSR
2022-10-21 Added new binary
2022-10-21 Fix in second port version number
2022-10-21 Firmware now counts filament current in 0.1 mA
2022-10-21 Cli now uses mA in frontend
2022-10-21 Increase version number
2022-10-21 Timeout fix for beamon sequence
2022-10-21 Increase ramp speed since counting in 100 uA steps
2022-10-21 Now waiting for filseta response
2022-10-21 Fixed serial buffer handling
2022-10-21 Eguncom now waits for filseta in condition for seta and filseta
2022-10-21 Always reporting SET current even if disabled
2022-10-21 Python library now allows setting filament current in 100 uA steps
2022-10-22 Removing redundant code
2022-10-22 Minor change
2022-10-24 Bugfix
2022-10-24 Placeholder for current controller extension responses
2022-10-24 Rebuilt firmware
2022-11-04 Began schematic for DAC & ADC based interface and controller board
2022-11-04 Finished schematic
2022-11-07 FInished Schematic, assigned footprints, added 230V PSU
2022-11-07 Began place and route
2022-11-08 Continue place and route, minor fixes
2022-11-11 Controller:
    * Implemented slope limit for high voltages
    * Removed redundant constants to reduce memory usage
    * Output enable / disable is now controlled by voltage on HV supplies (to guarantee ramping operation)
    * Removed code for controlling primary side SSR
    * Removed serial commands that allowed enabling / disabling PSUs (since this is now controlled by voltage setting)
    * Reduced sized of parsing buffers for complete messages
2022-11-11 Modified to match firmware, version 0.0.26
    * Removed setPSUEnable and setPSUDisable (not supported by controller any more)
    * Unit conversion of current is handled in firmware for setting filament current
    * Filament current report is now correctly parsed also for seta: responses
2022-11-11 Correctly disabling filament
2022-11-11 Update binary
2022-11-22 Bugfixes and new features for 0.0.36
    * Ringbuffer always keeps a single byte empty to prevent overrun
    * Fixed bug in isAvailable that inverted correct result
    * Allows to disable shutdown at interpreter exit (shutdown_on_terminate(False))
    * Beamon timeout increased to 1200 seconds
    * Synchronous waiting for filseta on filon, filoff and setting filament current
    * Scaling of filament current
2022-11-22 PWM out now has per channel scaling factor, new default target values
2022-11-23 Added get_status, repr and str
2022-11-24 Added noprotection argument to setFilamentCurrent method
2022-11-25 Added support to set filament current in beamOn command
2022-11-25 Beamon requires filament to be disabled in the beginning
2022-11-28 Modifications to allow configuration of magic values (not finished)
2022-11-29 Rebuilding controller firmware, updating Makefile
2022-11-29 New commands for setting and getting configurable parameters
2022-11-29 Missing message handlers
2022-11-29 Added missing message handlers for serial 1
2022-11-29 Missing callbacks
2022-11-29 Fixed parsing bug in serial message for setters
2022-11-29 Minor bug with message generation for setting configuration parameters
2022-11-29 Minor bug in parsing messages
2022-11-29 Missing cathode setter in serial1
2022-11-29 Setter command handling, write EEPROM method
2022-11-29 New binary
2022-11-29 Fixed assignment of PSUs during beamon
2022-11-29 Minor fix in beamon
2022-11-29 Fixed typo
2022-11-30 Missing format string
2022-11-30 Index fixes
2022-11-30 Updated binary
2022-12-02 Invalid correction factor for currents in __str__
2022-12-06 Allow calibration of ADC readings from HVPS
2022-12-06 Methods for calibration of HVPS readings
2022-12-06 Waiting for stable voltages on HVPS (only works after calibration)
2023-10-17 Added limiting difference between W and K, adding blank and unblank to firmware
2023-10-17 Blank and unblank into Python code
2023-10-18 Also bump version ID
2023-10-18 Update version information
2023-10-18 BUmp version and update setup.cfg (no automatic tag)
2023-10-18 Serial bugfixes
2023-10-18 Getting target voltages fixed
2023-10-18 Rebuild
2023-10-18 Fixed current setting, bump version
2023-10-18 Expose default setting function
2023-10-18 Implement maximum difference between W and K in both directions
2023-10-18 Minor modifications
2023-10-18 Removing querying of target voltage and current limit for beam mode on serial0 to save progmem
2023-10-18 New calibrations
